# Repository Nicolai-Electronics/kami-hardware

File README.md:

# Kami: a simple epaper badge

Kami is a modernized re-imagining of the SHA2017 epaper badge by Badge.Team.

## Documentation

Need the schematic? [It's in this repository as a PDF file](schematic.pdf).

## License

This hardware design may be used under the terms of the [CERN-OHL-P](LICENSE) license.

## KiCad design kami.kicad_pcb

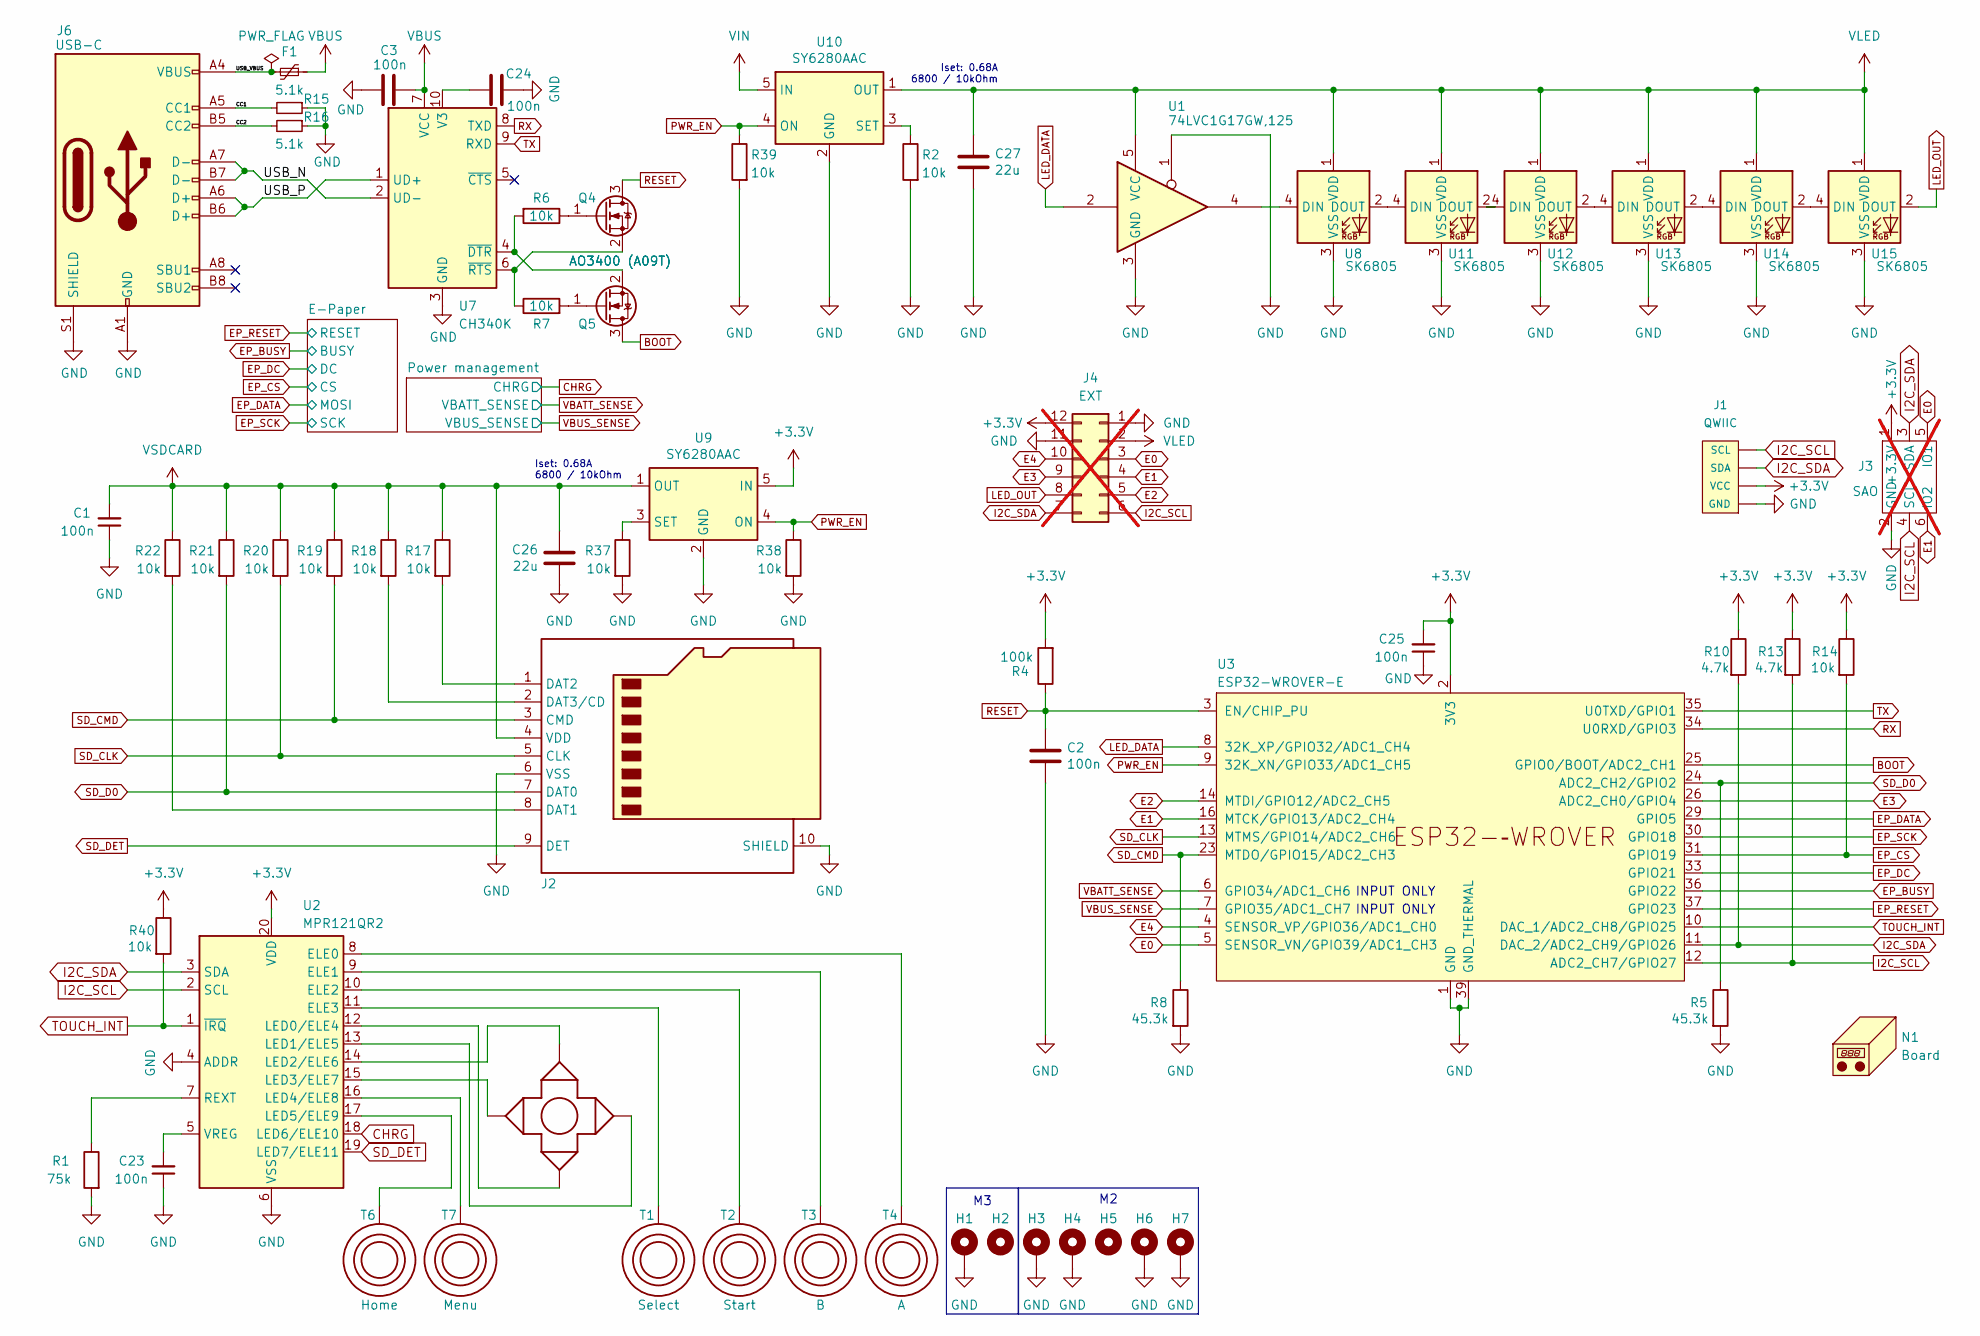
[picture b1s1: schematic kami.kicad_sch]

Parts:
C1, C2, C3, C23, C24, C25: 100n; C_0402_1005Metric; LCSC C307331
C26, C27: 22u; C_0805_2012Metric; LCSC C45783
F1: 1A; Fuse_0805_2012Metric; LCSC C269107
H1: MountingHole_3.2mm_M3_DIN965_Pad_TopOnly
H2: MountingHole_3.2mm_M3_DIN965
H3, H4, H6, H7: MountingHole_2.7mm_M2.5_Pad_TopOnly
H5: MountingHole_2.7mm_M2.5_DIN965
J1: QWIIC; Qwiic 1X04_1MM_RA_GND; LCSC C160404
J2: Micro_SD_Card; SD_Card-micro_socket_A; LCSC C7529389
J3: SAO; SAO Female THT Labels; LCSC C2829893; not fitted
J4: EXT; EXPANSION; not fitted
J6: USB-C; USB_C_Receptacle_HRO_TYPE-C-31-M-12; LCSC C165948
N1: Board; board
Q4, Q5: AO3400 (A09T); SOT-23; LCSC C2938367
R1: 75k; R_0402_1005Metric; LCSC C25798
R2, R6, R7, R14, R17, R18, R19, R20, R21, R22, R37, R38, R39, R40: 10k; R_0402_1005Metric; LCSC C25744
R4: 100k; R_0402_1005Metric; LCSC C25741
R5, R8: 45.3k; R_0402_1005Metric; LCSC C26980
R10, R13: 4.7k; R_0402_1005Metric; LCSC C25940
R15, R16: 5.1k; R_0402_1005Metric; LCSC C25905
T1: Select; TOUCH_SELECT
T2: Start; TOUCH_SELECT
T3: B; TOUCH_BUTTON
T4: A; TOUCH_BUTTON
T5: Cross; TOUCH_CROSS
T6: Home; home
T7: Menu; menu
U1: 74LVC1G17GW,125; SOT-353_SC-70-5; LCSC C426705
U2: MPR121QR2; UQFN-20_3x3mm_P0.4mm; LCSC C91322
U3: ESP32-WROVER-E; LCSC C529589
U7: CH340K; SSOP-10-1EP_3.9x4.9mm_P1mm_EP2.1x3.3mm; LCSC C18208922
U8, U11, U12, U13, U14, U15: SK6805; SK6805-EC20; LCSC C2890036
U9, U10: SY6280AAC; SOT-23-5; LCSC C55136

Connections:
+3.3V: C25.2, J1.2 (VCC), J3.1 (+3.3V), J4.12, R4.2, R10.1, R13.1, R14.1, R40.1, U2.20 (VDD), U3.2 (3V3), U9.5 (IN); also elsewhere on the board
/CC1: J6.A5 (CC1), R15.2
/CC2: J6.B5 (CC2), R16.2
/USB_N: J6.A7 (D-), J6.B7 (D-), U7.2 (UD-)
/USB_P: J6.A6 (D+), J6.B6 (D+), U7.1 (UD+)
/USB_VBUS: F1.2, J6.A4 (VBUS), J6.A9 (VBUS), J6.B4 (VBUS), J6.B9 (VBUS)
BOOT: Q5.3 (D), U3.25 (GPIO0/BOOT/ADC2_CH1)
CHRG: U2.18 (LED6/ELE10); also elsewhere on the board
E0: J3.5 (IO1), J4.3, U3.5 (SENSOR_VN/GPIO39/ADC1_CH3)
E1: J3.6 (IO2), J4.4, U3.16 (MTCK/GPIO13/ADC2_CH4)
E2: J4.5, U3.14 (MTDI/GPIO12/ADC2_CH5)
E3: J4.9, U3.26 (ADC2_CH0/GPIO4)
E4: J4.10, U3.4 (SENSOR_VP/GPIO36/ADC1_CH0)
EP_BUSY: U3.36 (GPIO22); also elsewhere on the board
EP_CS: R14.2, U3.31 (GPIO19); also elsewhere on the board
EP_DATA: U3.29 (GPIO5); also elsewhere on the board
EP_DC: U3.33 (GPIO21); also elsewhere on the board
EP_RESET: U3.37 (GPIO23); also elsewhere on the board
EP_SCK: U3.30 (GPIO18); also elsewhere on the board
GND: C1.1, C2.2, C3.2, C23.1, C24.2, C25.1, C26.2, C27.2, H1.1, H3.1, H4.1, H6.1, H7.1, J1.1 (GND), J1.5, J1.6, J2.6 (VSS), J2.10 (SHIELD), J3.2 (GND), J4.1, J4.11, J6.A1 (GND), J6.A12 (GND), J6.B1 (GND), J6.B12 (GND), J6.S1 (SHIELD), R1.2, R2.2, R5.2, R8.2, R15.1, R16.1, R37.2, R38.2, R39.2, U1.1, U1.3 (GND), U2.4 (ADDR), U2.6 (VSS), U3.1 (GND), U3.15 (GND), U3.38 (GND), U3.39 (GND_THERMAL), U7.3 (GND), U7.11 (GND), U8.3 (VSS), U9.2 (GND), U10.2 (GND), U11.3 (VSS), U12.3 (VSS), U13.3 (VSS), U14.3 (VSS), U15.3 (VSS); also elsewhere on the board
I2C_SCL: J1.4 (SCL), J3.4 (SCL), J4.6, R13.2, U2.2 (SCL), U3.12 (ADC2_CH7/GPIO27)
I2C_SDA: J1.3 (SDA), J3.3 (SDA), J4.7, R10.2, U2.3 (SDA), U3.11 (DAC_2/ADC2_CH9/GPIO26)
LED_DATA: U1.2, U3.8 (32K_XP/GPIO32/ADC1_CH4)
LED_OUT: J4.8, U15.2 (DOUT)
unnamed: J2.8 (DAT1), R22.2
unnamed: J2.1 (DAT2), R17.2
unnamed: J2.2 (DAT3/CD), R18.2
unnamed: Q4.1 (G), R6.1
unnamed: Q4.2 (S), R7.1, U7.6 (~RTS)
unnamed: Q5.1 (G), R7.2
unnamed: Q5.2 (S), R6.2, U7.4 (~DTR)
unnamed: T4.1, U2.8 (ELE0)
unnamed: T3.1, U2.9 (ELE1)
unnamed: T2.1, U2.10 (ELE2)
unnamed: T1.1, U2.11 (ELE3)
unnamed: T5.3, U2.12 (LED0/ELE4)
unnamed: T5.2, U2.13 (LED1/ELE5)
unnamed: T5.1, U2.14 (LED2/ELE6)
unnamed: T5.4, U2.15 (LED3/ELE7)
unnamed: T7.1, U2.16 (LED4/ELE8)
unnamed: T6.1, U2.17 (LED5/ELE9)
unnamed: R1.1, U2.7 (REXT)
unnamed: C23.2, U2.5 (VREG)
unnamed: C24.1, U7.10 (V3)
unnamed: U1.4, U8.4 (DIN)
unnamed: R37.1, U9.3 (SET)
unnamed: R2.1, U10.3 (SET)
unnamed: U8.2 (DOUT), U11.4 (DIN)
unnamed: U11.2 (DOUT), U12.4 (DIN)
unnamed: U12.2 (DOUT), U13.4 (DIN)
unnamed: U13.2 (DOUT), U14.4 (DIN)
unnamed: U14.2 (DOUT), U15.4 (DIN)
PWR_EN: R38.1, R39.1, U3.9 (32K_XN/GPIO33/ADC1_CH5), U9.4 (ON), U10.4 (ON)
RESET: C2.1, Q4.3 (D), R4.1, U3.3 (EN/CHIP_PU)
RX: U3.34 (U0RXD/GPIO3), U7.8 (TXD)
SD_CLK: J2.5 (CLK), R20.2, U3.13 (MTMS/GPIO14/ADC2_CH6)
SD_CMD: J2.3 (CMD), R8.1, R19.2, U3.23 (MTDO/GPIO15/ADC2_CH3)
SD_D0: J2.7 (DAT0), R5.1, R21.2, U3.24 (ADC2_CH2/GPIO2)
SD_DET: J2.9 (DET), U2.19 (LED7/ELE11)
TOUCH_INT: R40.2, U2.1 (~IRQ), U3.10 (DAC_1/ADC2_CH8/GPIO25)
TX: U3.35 (U0TXD/GPIO1), U7.9 (RXD)
VBATT_SENSE: U3.6 (GPIO34/ADC1_CH6); also elsewhere on the board
VBUS: C3.1, F1.1, U7.7 (VCC); also elsewhere on the board
VBUS_SENSE: U3.7 (GPIO35/ADC1_CH7); also elsewhere on the board
VIN: U10.5 (IN); also elsewhere on the board
VLED: C27.1, J4.2, U1.5 (VCC), U8.1 (VDD), U10.1 (OUT), U11.1 (VDD), U12.1 (VDD), U13.1 (VDD), U14.1 (VDD), U15.1 (VDD)
VSDCARD: C1.2, C26.1, J2.4 (VDD), R17.1, R18.1, R19.1, R20.1, R21.1, R22.1, U9.1 (OUT)

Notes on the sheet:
Iset: 0.68A 6800 / 10kOhm
INPUT ONLY

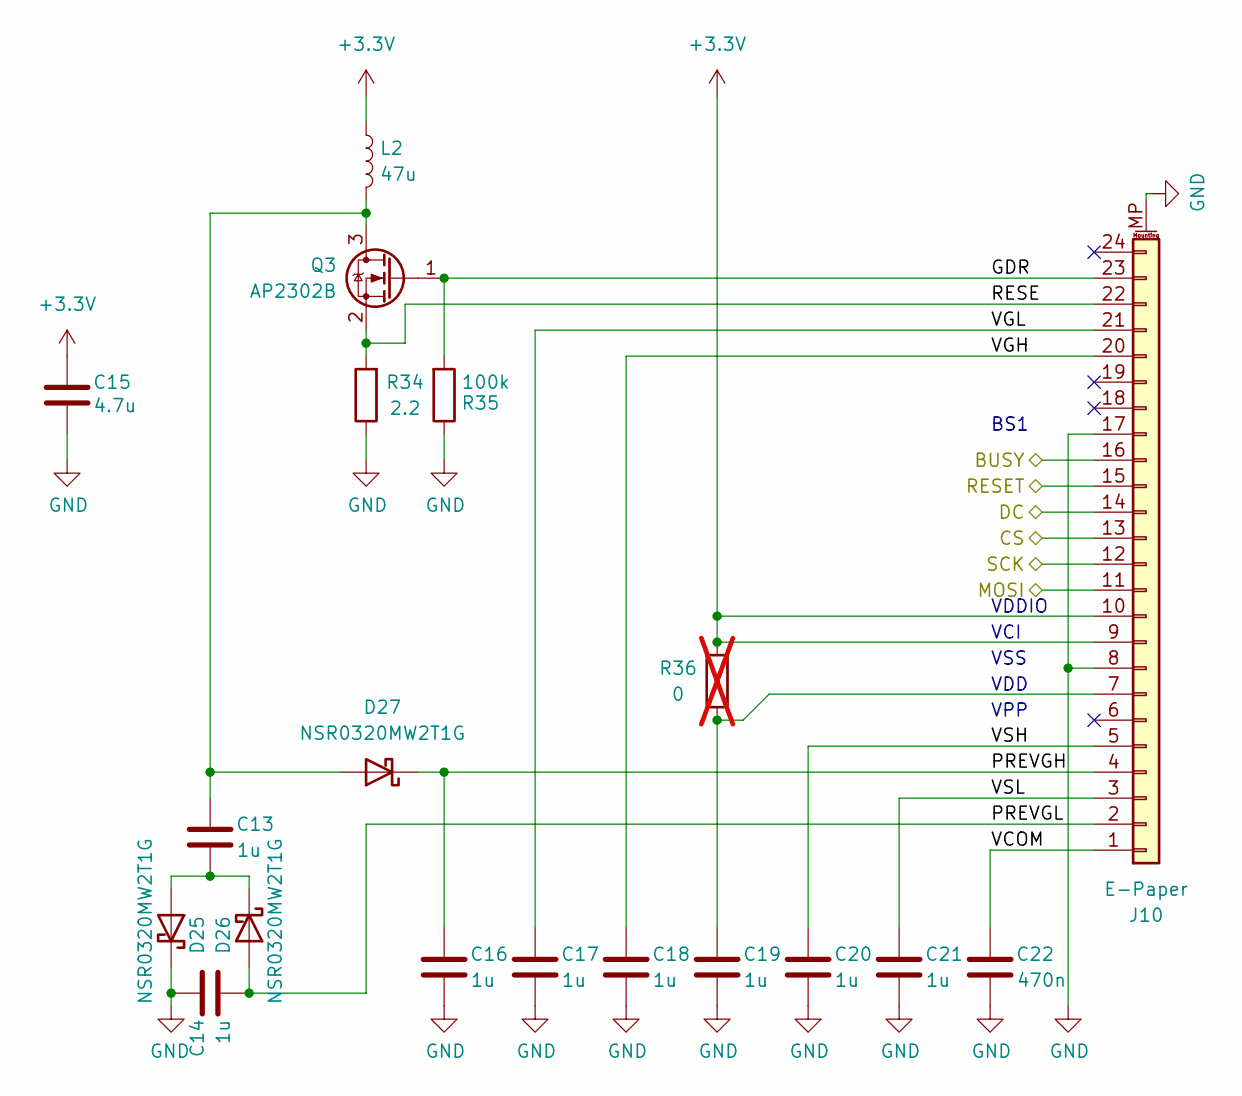
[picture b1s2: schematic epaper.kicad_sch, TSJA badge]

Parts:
C13, C14, C16, C17, C18, C19, C20, C21: 1u; C_0603_1608Metric; LCSC C5199872
C15: 4.7u; C_0603_1608Metric; LCSC C69335
C22: 470n; C_0603_1608Metric; LCSC C1623
D25, D26, D27: NSR0320MW2T1G; D_SOD-323; LCSC C48192
J10: E-Paper; Hirose_FH12-24S-0.5SH_1x24-1MP_P0.50mm_Horizontal; LCSC C202112
L2: 47u; L_1210_3225Metric; LCSC C83083
Q3: AP2302B; SOT-23; LCSC C406812
R34: 2.2; R_0805_2012Metric; LCSC C2907304
R35: 100k; R_0402_1005Metric; LCSC C25741
R36: 0; R_0402_1005Metric; not fitted

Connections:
+3.3V: C15.2, J10.9, J10.10, L2.1, R36.1; also elsewhere on the board
/E-Paper/GDR: J10.23, Q3.1 (G), R35.2
/E-Paper/PREVGH: C16.2, D27.1 (K), J10.4
/E-Paper/PREVGL: C14.1, D26.2 (A), J10.2
/E-Paper/RESE: J10.22, Q3.2 (S), R34.2
/E-Paper/VCOM: C22.2, J10.1
/E-Paper/VGH: C18.2, J10.20
/E-Paper/VGL: C17.2, J10.21
/E-Paper/VSH: C20.2, J10.5
/E-Paper/VSL: C21.2, J10.3
EP_BUSY: J10.16; also elsewhere on the board
EP_CS: J10.13; also elsewhere on the board
EP_DATA: J10.11; also elsewhere on the board
EP_DC: J10.14; also elsewhere on the board
EP_RESET: J10.15; also elsewhere on the board
EP_SCK: J10.12; also elsewhere on the board
GND: C14.2, C15.1, C16.1, C17.1, C18.1, C19.1, C20.1, C21.1, C22.1, D25.1 (K), J10.8, J10.17, J10.MP (MountPin), R34.1, R35.1; also elsewhere on the board
unnamed: C13.1, D25.2 (A), D26.1 (K)
unnamed: C13.2, D27.2 (A), L2.2, Q3.3 (D)
unnamed: C19.2, J10.7, R36.2

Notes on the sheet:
VDD
VSS
BS1
VDDIO
VCI
VPP

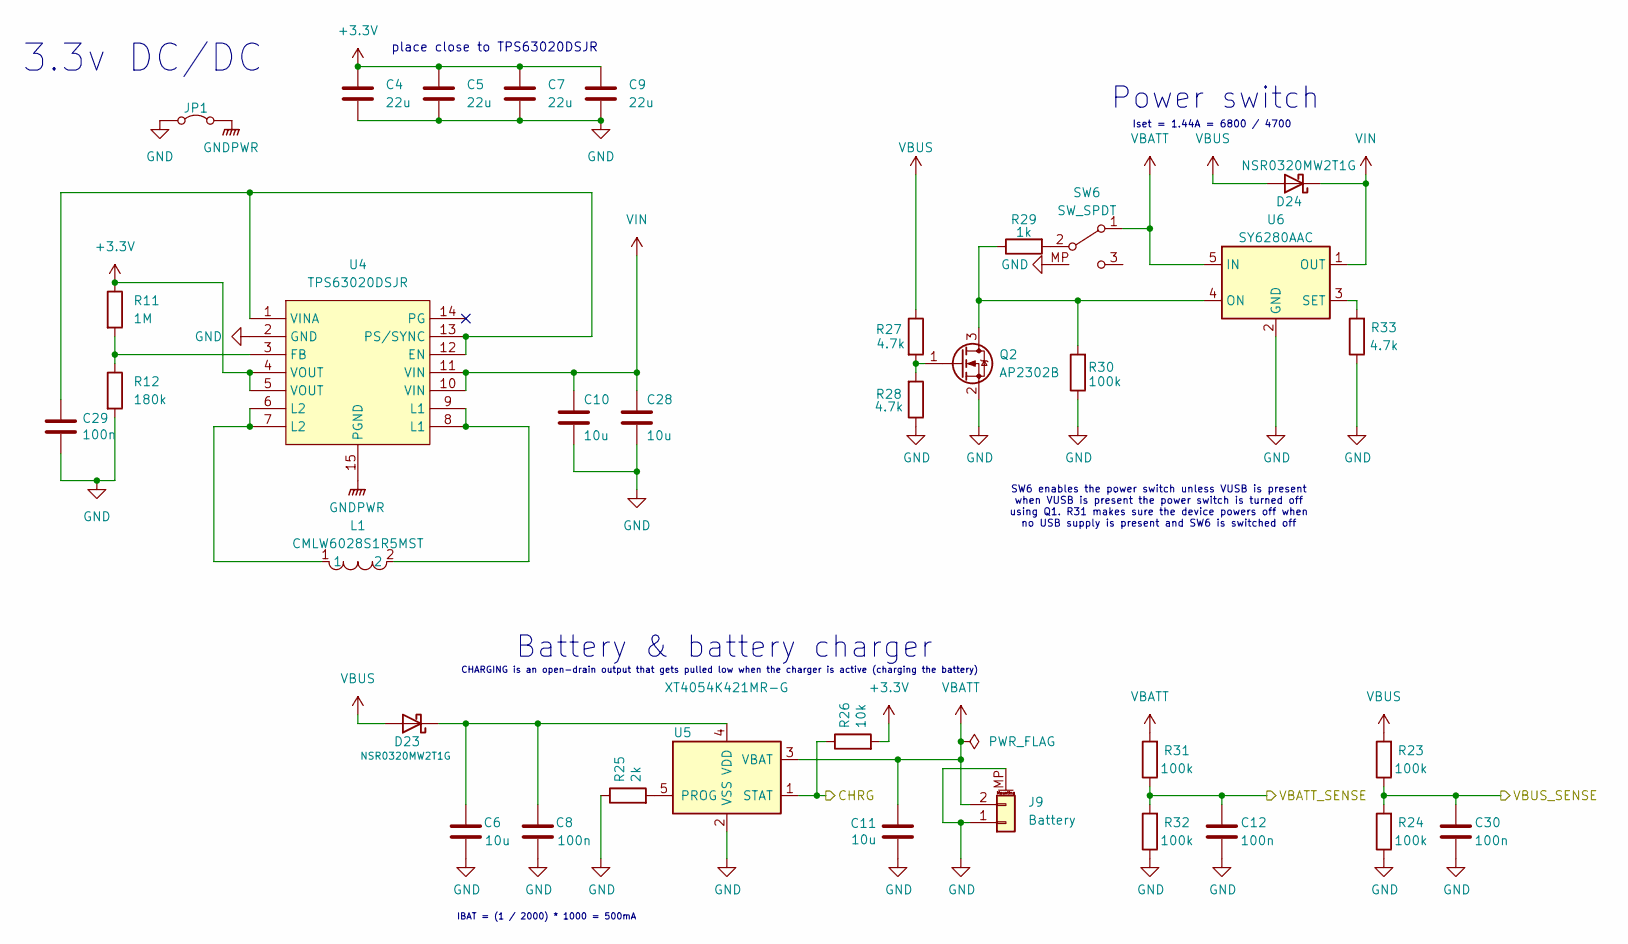
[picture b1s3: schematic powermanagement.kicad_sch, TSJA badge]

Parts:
C4, C5, C7, C9: 22u; C_0805_2012Metric; LCSC C45783
C6, C10, C11, C28: 10u; C_0805_2012Metric; LCSC C3039694
C8, C12, C29, C30: 100n; C_0402_1005Metric; LCSC C307331
D23, D24: NSR0320MW2T1G; D_SOD-323; LCSC C48192
J9: Battery; JST_S2B-ZR-SM4A-TF(LF)(SN); LCSC C265329
JP1: NetTie-2_SMD_Pad0.5mm
L1: CMLW6028S1R5MST; IND-SMD_L6.0-W6.0; LCSC C431354
Q2: AP2302B; SOT-23; LCSC C406812
R11: 1M; R_0402_1005Metric_Pad0.72x0.64mm_HandSolder; LCSC C26083
R12: 180k; R_0402_1005Metric_Pad0.72x0.64mm_HandSolder; LCSC C2909325
R23, R24, R30, R31, R32: 100k; R_0402_1005Metric; LCSC C25741
R25: 2k; R_0402_1005Metric; LCSC C4109
R26: 10k; R_0402_1005Metric; LCSC C25744
R27, R28, R33: 4.7k; R_0402_1005Metric; LCSC C25940
R29: 1k; R_0402_1005Metric; LCSC C11702
SW6: SW_SPDT; SW_SPDT_PCM12_MP; LCSC C319020
U4: TPS63020DSJR; VSON-14_L4.0-W3.0-P0.50-BL-EP_TI_DSJ; LCSC C15483
U5: XT4054K421MR-G; SOT-23-5; LCSC C141405
U6: SY6280AAC; SOT-23-5; LCSC C55136

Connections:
+3.3V: C4.1, C5.1, C7.1, C9.1, R11.1, R26.2, U4.4 (VOUT), U4.5 (VOUT); also elsewhere on the board
CHRG: R26.1, U5.1 (STAT); also elsewhere on the board
GND: C4.2, C5.2, C6.1, C7.2, C8.1, C9.2, C10.2, C11.2, C12.2, C28.2, C29.2, C30.2, J9.1, J9.MP (MountPin), JP1.1 (A), Q2.2 (S), R12.2, R24.1, R25.1, R28.1, R30.1, R32.1, R33.1, SW6.MP, U4.2 (GND), U5.2 (VSS), U6.2 (GND); also elsewhere on the board
GNDPWR: JP1.2 (B), U4.15 (PGND)
unnamed: C6.2, C8.2, D23.1 (K), U5.4 (VDD)
unnamed: L1.1, U4.6 (L2), U4.7 (L2)
unnamed: L1.2, U4.8 (L1), U4.9 (L1)
unnamed: Q2.3 (D), R29.1, R30.2, U6.4 (ON)
unnamed: Q2.1 (G), R27.2, R28.2
unnamed: R29.2, SW6.2 (B)
unnamed: C29.1, U4.1 (VINA), U4.12 (EN), U4.13 (PS/SYNC)
unnamed: R11.2, R12.1, U4.3 (FB)
unnamed: R25.2, U5.5 (PROG)
unnamed: R33.2, U6.3 (SET)
VBATT: C11.1, J9.2, R31.2, SW6.1 (A), U5.3 (VBAT), U6.5 (IN)
VBATT_SENSE: C12.1, R31.1, R32.2; also elsewhere on the board
VBUS: D23.2 (A), D24.2 (A), R23.2, R27.1; also elsewhere on the board
VBUS_SENSE: C30.1, R23.1, R24.2; also elsewhere on the board
VIN: C10.1, C28.1, D24.1 (K), U4.10 (VIN), U4.11 (VIN), U6.1 (OUT); also elsewhere on the board

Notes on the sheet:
CHARGING is an open-drain output that gets pulled low when the charger is active (charging the battery)
place close to TPS63020DSJR
Power switch
Battery & battery charger
3.3v DC/DC
SW6 enables the power switch unless VUSB is present when VUSB is present the power switch is turned off using Q1. R31 makes sure the device powers off when no USB supply is present and SW6 is switched off
IBAT = (1 / 2000) * 1000 = 500mA
Iset = 1.44A = 6800 / 4700

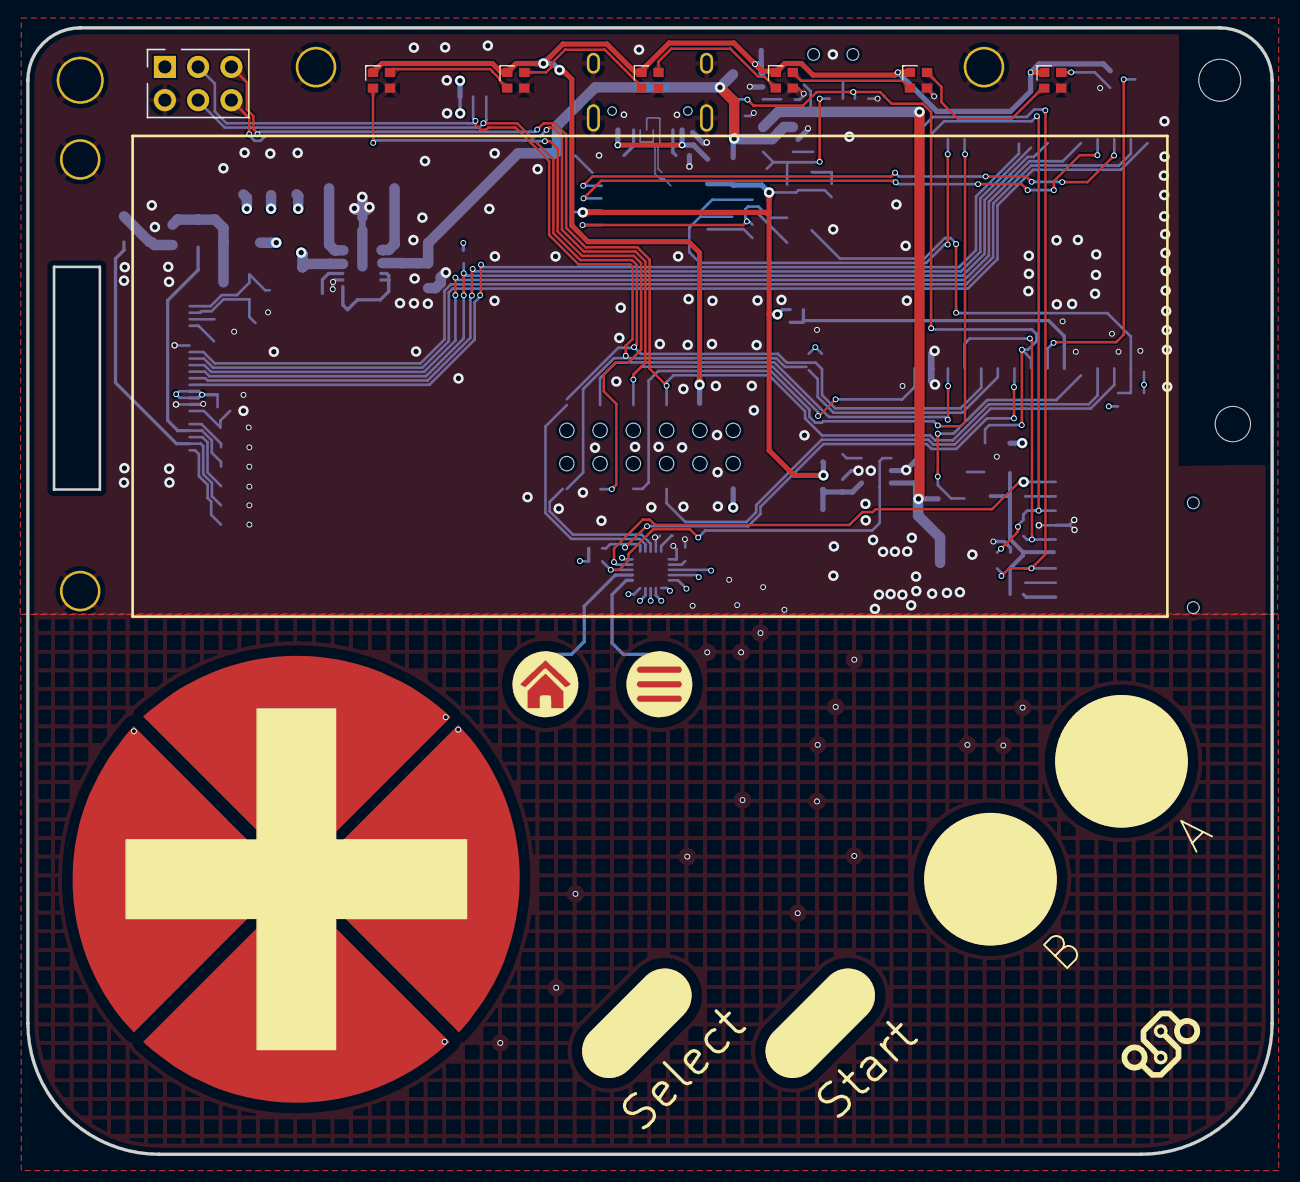
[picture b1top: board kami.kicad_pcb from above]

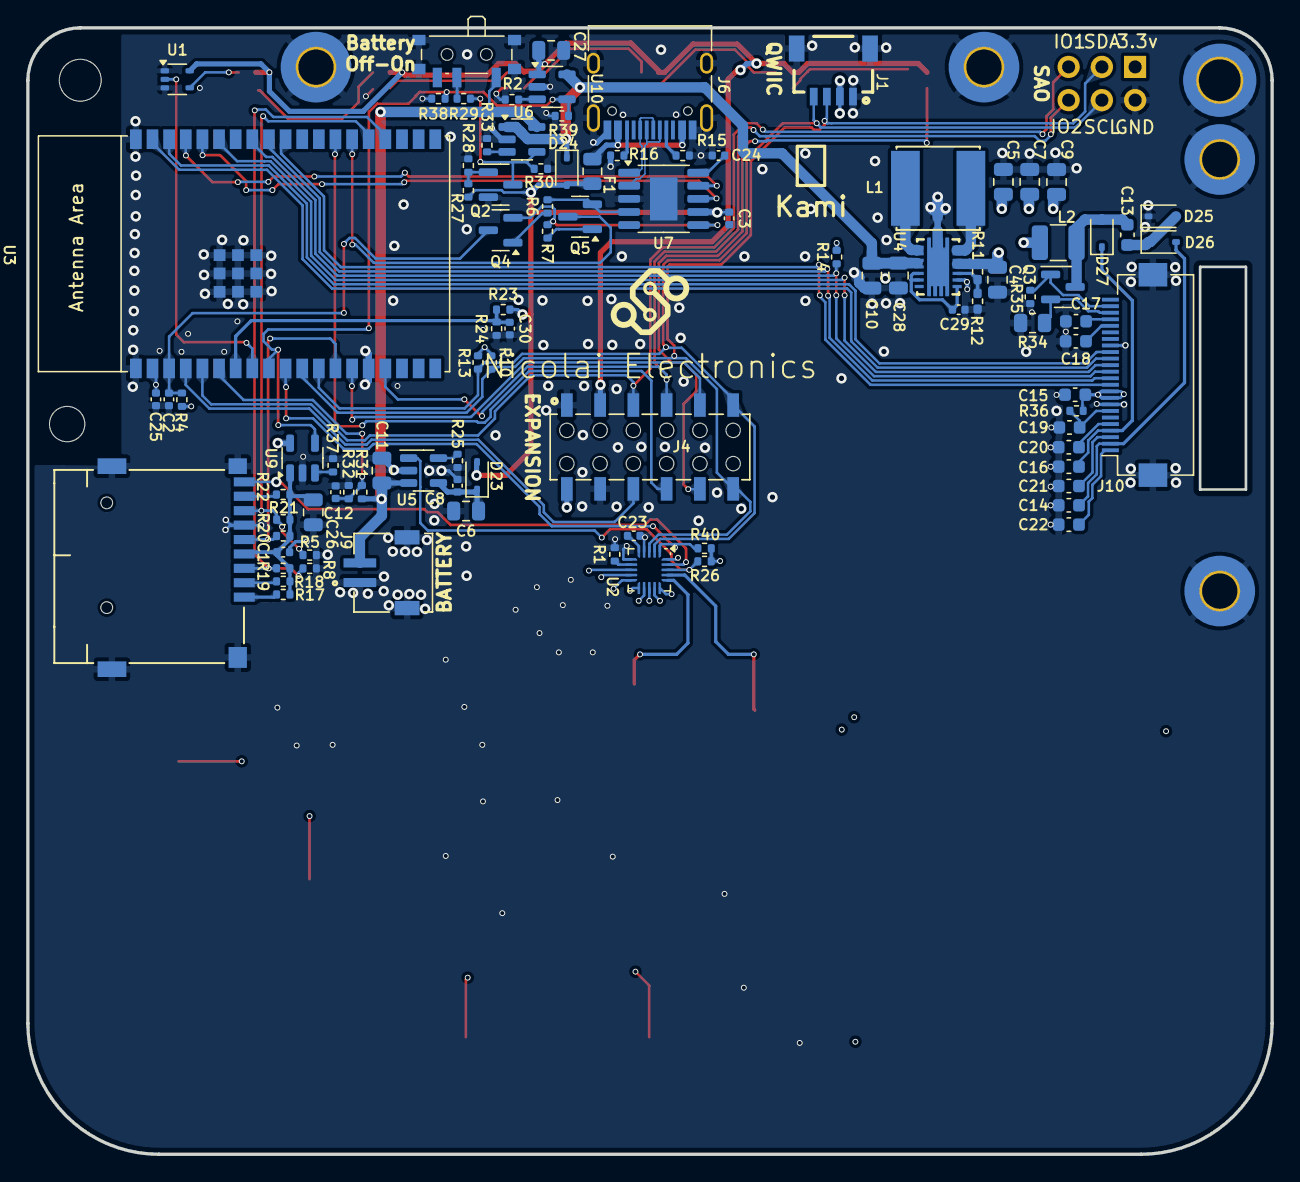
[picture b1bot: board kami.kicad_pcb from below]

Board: 4 copper layers, 95.0 x 86.0 mm, 118 parts (104 on the bottom side), 91 nets.

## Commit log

2024-12-06 Use DC/DC from WHY badge
2024-12-07 Small fixes
2024-12-08 No DRC errors
2024-12-08 Cleanup & tweaks
2024-12-08 Fix some routing issues, add GND vias, add capacitor for M1, add spacing between vias for ground to pour inbetween.
2024-12-08 Apply fixes proposed by Paul
2024-12-08 Small fix to ground close to R14
2024-12-08 Fill out BOM, add labels to PCB
2024-12-09 Route captouch traces through inner layer, add two buttons, remove vibration motor
2024-12-22 Add production files
2025-05-20 Rename to Kami
2025-05-20 Changes for production version
2025-05-20 Add README
2025-05-20 Add schematic

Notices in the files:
epaper.kicad_sch:
License: CERN Open Hardware Licence Version 2 - Permissive
